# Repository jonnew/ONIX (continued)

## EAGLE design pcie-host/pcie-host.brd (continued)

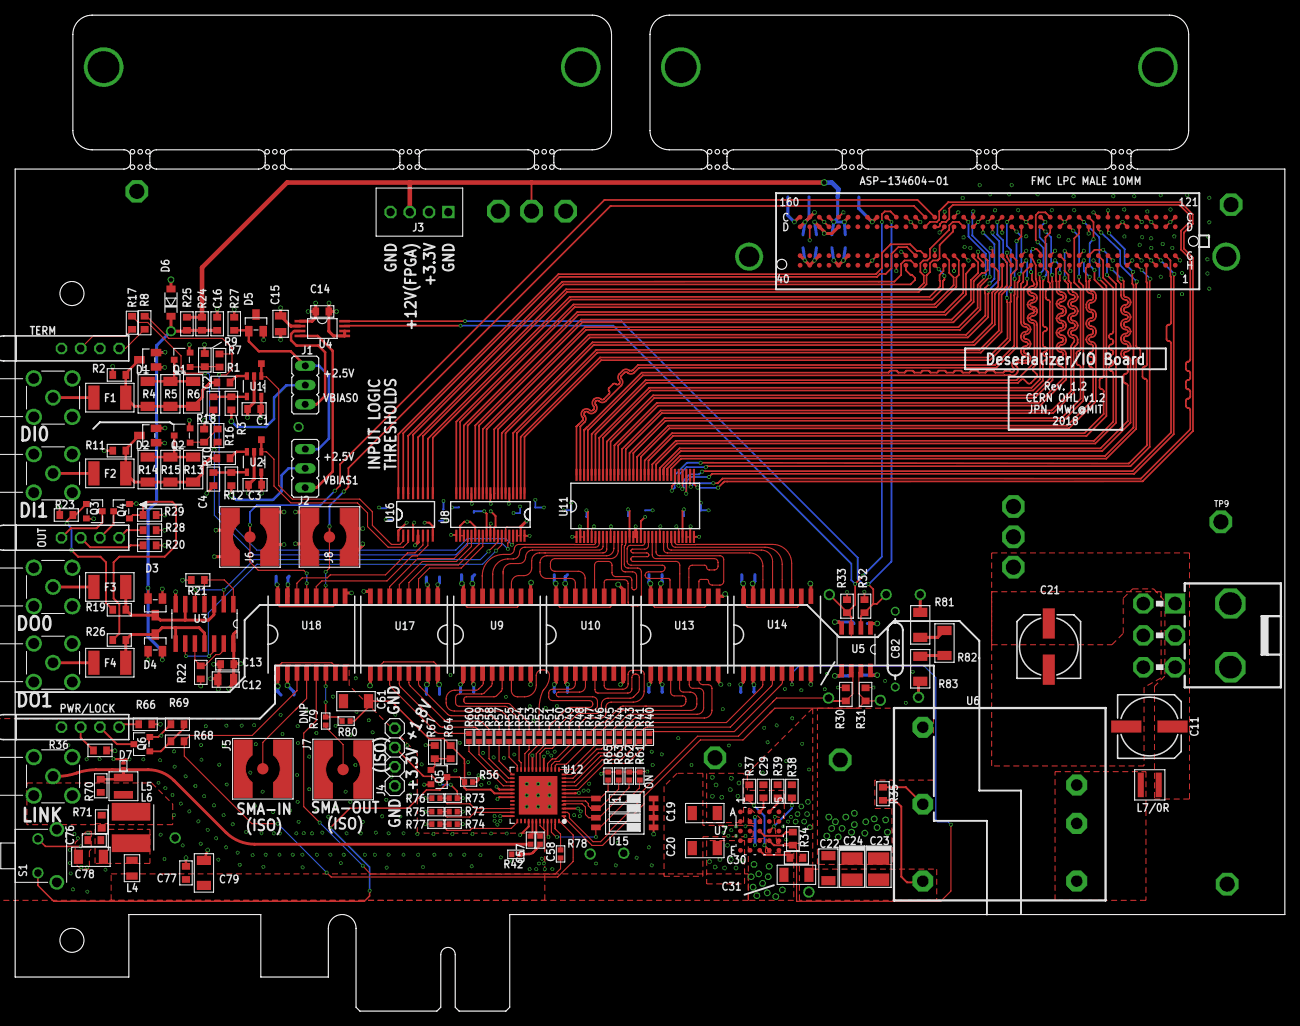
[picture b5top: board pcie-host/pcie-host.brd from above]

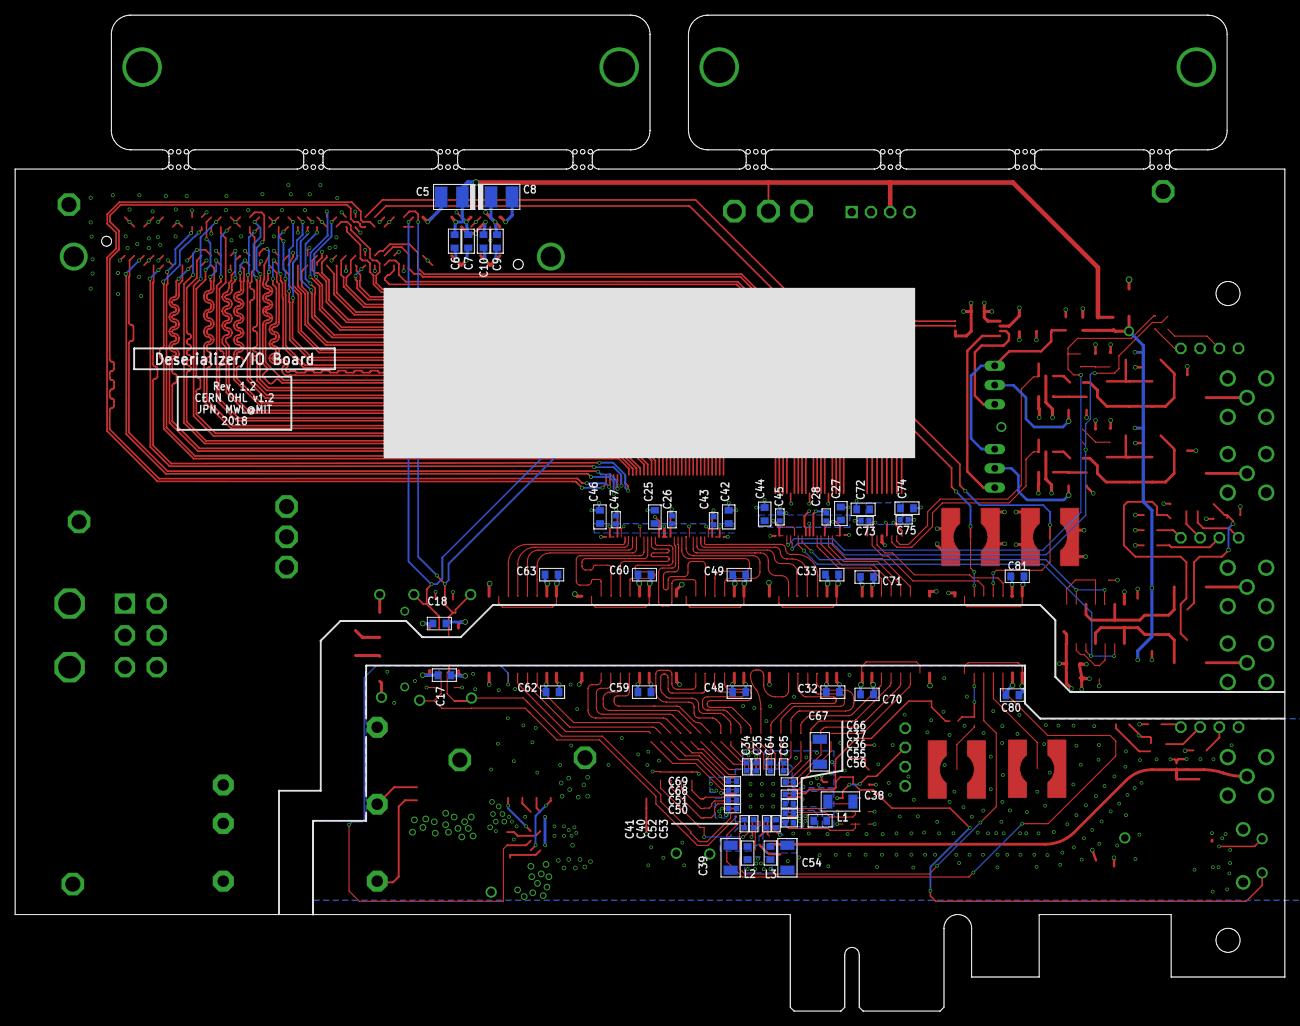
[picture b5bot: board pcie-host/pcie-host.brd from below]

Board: 4 copper layers, 167.6 x 131.5 mm, 253 parts (59 on the bottom side), 208 nets.

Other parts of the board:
C82: 2.2nF,X/Y; C900
D7: SESD0402X1UN-0020-090; 0402P-DFN
DI0: SMA002; SMA_JACK_CONREVSMA002-G
DO0: SMA002; SMA_JACK_CONREVSMA002-G
R81, R83: 330k, 1kV; 1206
R82: 330k,1kV; 1206

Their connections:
DOUTP_F: D7.C; also elsewhere on the board
GND: C82.1, DI0.GND$1, DI0.GND$2, DI0.GND$3, DI0.GND$4, DO0.GND$1, DO0.GND$2, DO0.GND$3, DO0.GND$4, R81.2; also elsewhere on the board
GND_ISO: C82.2, D7.A, R83.1; also elsewhere on the board
unnamed: R81.1, R82.2
unnamed: R82.1, R83.2

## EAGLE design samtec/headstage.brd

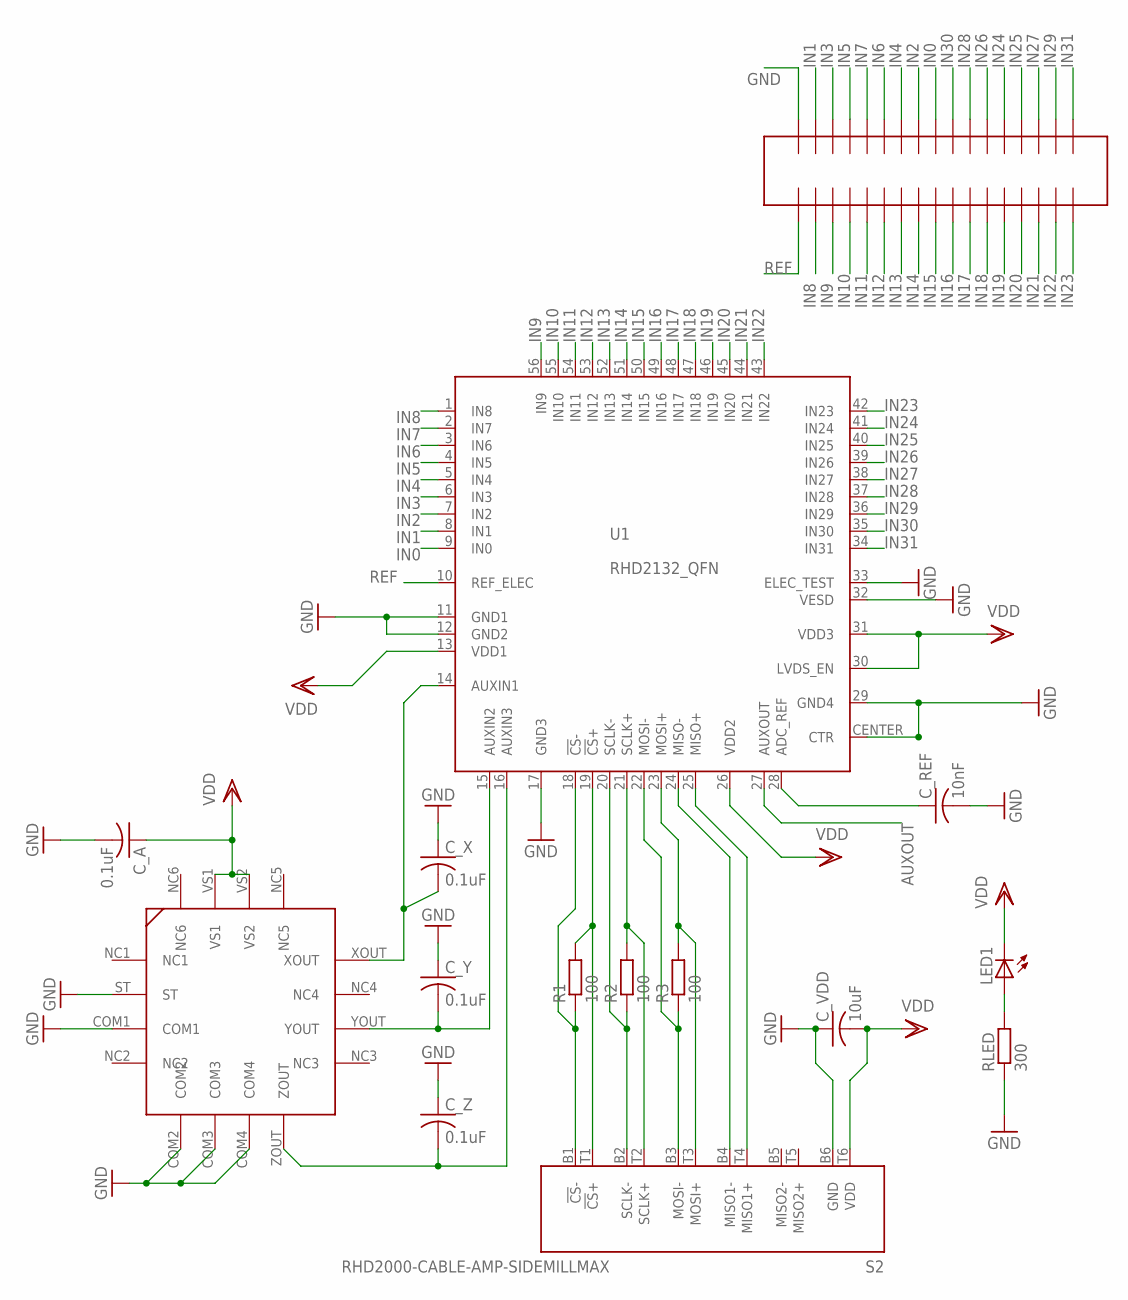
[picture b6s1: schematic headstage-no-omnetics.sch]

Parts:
C_A: 0.1uF; C0402K
C_REF: 10nF; C0402K
C_VDD: 10uF; C0805
C_X: 0.1uF; C0402K
C_Y: 0.1uF; C0402K
C_Z: 0.1uF; C0402K
LED1: LEDCHIPLED_0805; CHIPLED_0805
R1, R2, R3: 100; R0402
RLED: 300; R0402
S2: RHD2000-CABLE-AMP-SIDEMILLMAX; MILLMAX-12PIN
U1: RHD2132_QFN; QFN56_8_X_8_LARGE
U$1: ADXL335
U$2: FTSH-117BOARD-END; FTSH-117-END

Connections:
ADC_REF: C_REF.1, U1.28 (ADC_REF)
AUXOUT: U1.27 (AUXOUT)
CS+: R1.2, S2.T1 (!CS!+), U1.19 (!CS!+)
CS-: R1.1, S2.B1 (!CS!-), U1.18 (!CS!-)
GND: C_A.2, C_REF.2, C_VDD.1, C_X.1, C_Y.1, C_Z.1, RLED.1, S2.B6 (GND), U1.11 (GND1), U1.12 (GND2), U1.17 (GND3), U1.29 (GND4), U1.32 (VESD), U1.33 (ELEC_TEST), U1.CENTER (CTR), U$1.COM1, U$1.COM2, U$1.COM3, U$1.COM4, U$1.ST, U$2.P$34
IN0: U1.9 (IN0), U$2.P$26
IN1: U1.8 (IN1), U$2.P$33
IN2: U1.7 (IN2), U$2.P$27
IN3: U1.6 (IN3), U$2.P$32
IN4: U1.5 (IN4), U$2.P$28
IN5: U1.4 (IN5), U$2.P$31
IN6: U1.3 (IN6), U$2.P$29
IN7: U1.2 (IN7), U$2.P$30
IN8: U1.1 (IN8), U$2.P$2
IN9: U1.56 (IN9), U$2.P$3
IN10: U1.55 (IN10), U$2.P$4
IN11: U1.54 (IN11), U$2.P$5
IN12: U1.53 (IN12), U$2.P$6
IN13: U1.52 (IN13), U$2.P$7
IN14: U1.51 (IN14), U$2.P$8
IN15: U1.50 (IN15), U$2.P$9
IN16: U1.49 (IN16), U$2.P$10
IN17: U1.48 (IN17), U$2.P$11
IN18: U1.47 (IN18), U$2.P$12
IN19: U1.46 (IN19), U$2.P$13
IN20: U1.45 (IN20), U$2.P$14
IN21: U1.44 (IN21), U$2.P$15
IN22: U1.43 (IN22), U$2.P$16
IN23: U1.42 (IN23), U$2.P$17
IN24: U1.41 (IN24), U$2.P$22
IN25: U1.40 (IN25), U$2.P$21
IN26: U1.39 (IN26), U$2.P$23
IN27: U1.38 (IN27), U$2.P$20
IN28: U1.37 (IN28), U$2.P$24
IN29: U1.36 (IN29), U$2.P$19
IN30: U1.35 (IN30), U$2.P$25
IN31: U1.34 (IN31), U$2.P$18
LEDOUT: LED1.A, RLED.2
MISO1+: S2.T4 (MISO1+), U1.25 (MISO+)
MISO1-: S2.B4 (MISO1-), U1.24 (MISO-)
MOSI+: R3.2, S2.T3 (MOSI+), U1.23 (MOSI+)
MOSI-: R3.1, S2.B3 (MOSI-), U1.22 (MOSI-)
REF: U1.10 (REF_ELEC), U$2.P$1
SCLK+: R2.2, S2.T2 (SCLK+), U1.21 (SCLK+)
SCLK-: R2.1, S2.B2 (SCLK-), U1.20 (SCLK-)
VDD: C_A.1, C_VDD.2, LED1.C, S2.T6 (VDD), U1.13 (VDD1), U1.26 (VDD2), U1.30 (LVDS_EN), U1.31 (VDD3), U$1.VS1, U$1.VS2
XOUT: C_X.2, U1.14 (AUXIN1), U$1.XOUT
YOUT: C_Y.2, U1.15 (AUXIN2), U$1.YOUT
ZOUT: C_Z.2, U1.16 (AUXIN3), U$1.ZOUT

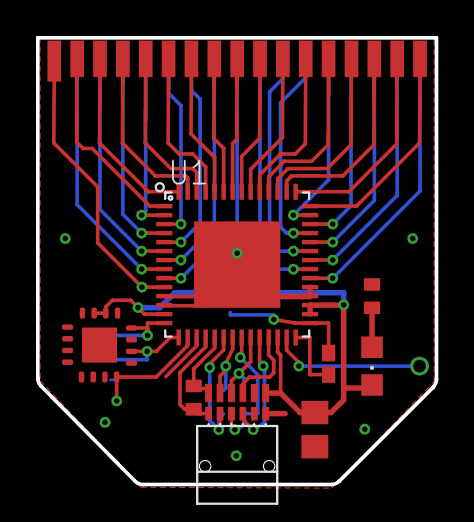
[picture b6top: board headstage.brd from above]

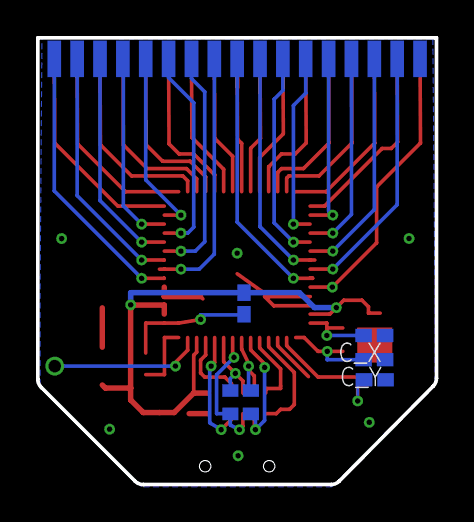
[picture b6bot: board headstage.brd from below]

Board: 2 copper layers, 22.1 x 24.8 mm, 15 parts (6 on the bottom side), 48 nets.
